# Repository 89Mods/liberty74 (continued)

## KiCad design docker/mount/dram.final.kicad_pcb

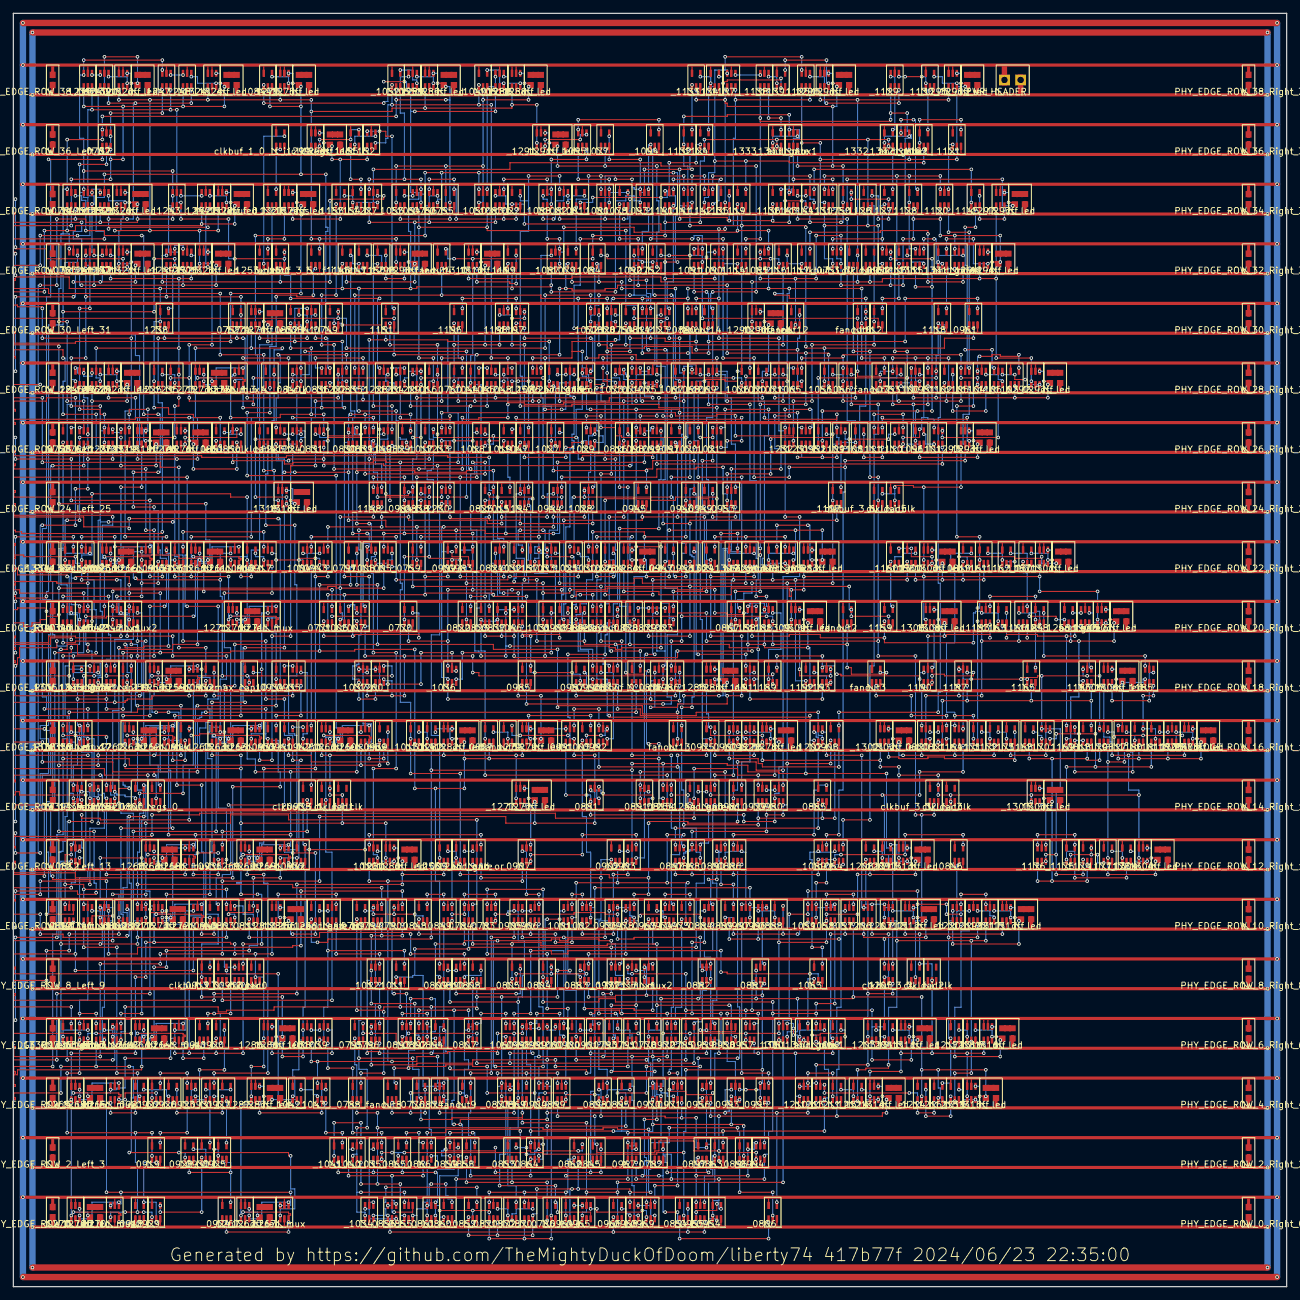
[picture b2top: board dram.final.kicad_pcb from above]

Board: 2 copper layers, 200.0 x 200.0 mm, 751 parts (0 on the bottom side), 638 nets.

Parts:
PHY_EDGE_ROW_0_Left_1, PHY_EDGE_ROW_0_Right_0, PHY_EDGE_ROW_2_Left_3, PHY_EDGE_ROW_2_Right_2, PHY_EDGE_ROW_4_Left_5, PHY_EDGE_ROW_4_Right_4, PHY_EDGE_ROW_6_Left_7, PHY_EDGE_ROW_6_Right_6, PHY_EDGE_ROW_8_Left_9, PHY_EDGE_ROW_8_Right_8, PHY_EDGE_ROW_10_Left_11, PHY_EDGE_ROW_10_Right_10, PHY_EDGE_ROW_12_Left_13, PHY_EDGE_ROW_12_Right_12, PHY_EDGE_ROW_14_Left_15, PHY_EDGE_ROW_14_Right_14, PHY_EDGE_ROW_16_Left_17, PHY_EDGE_ROW_16_Right_16, PHY_EDGE_ROW_18_Left_19, PHY_EDGE_ROW_18_Right_18, PHY_EDGE_ROW_20_Left_21, PHY_EDGE_ROW_20_Right_20, PHY_EDGE_ROW_22_Left_23, PHY_EDGE_ROW_22_Right_22, PHY_EDGE_ROW_24_Left_25, PHY_EDGE_ROW_24_Right_24, PHY_EDGE_ROW_26_Left_27, PHY_EDGE_ROW_26_Right_26, PHY_EDGE_ROW_28_Left_29, PHY_EDGE_ROW_28_Right_28, PHY_EDGE_ROW_30_Left_31, PHY_EDGE_ROW_30_Right_30, PHY_EDGE_ROW_32_Left_33, PHY_EDGE_ROW_32_Right_32, PHY_EDGE_ROW_34_Left_35, PHY_EDGE_ROW_34_Right_34, PHY_EDGE_ROW_36_Left_37, PHY_EDGE_ROW_36_Right_36, PHY_EDGE_ROW_38_Left_39, PHY_EDGE_ROW_38_Right_38: PWR_CAP; PWR_CAP_N
PWR_HEADER: PWR_HEADER; PWR_HEADER_N
_0749_, _0757_, _0759_, _0776_, _0782_, _0788_, _0791_, _0797_, _0822_, _0845_, _0846_, _0853_, _0911_, _0918_, _0921_, _0924_, _0945_, _0961_, _0985_, _1016_, _1077_, _1103_, _1126_, _1135_, _1168_, _1253__15: INV_74LVC1G04; INV_74LVC1G04_N
_0750_, _0752_, _0755_, _0800_, _0818_, _0819_, _0832_, _0850_, _0872_, _0878_, _0888_, _0896_, _0900_, _0912_, _0916_, _0919_, _0920_, _0922_, _0946_, _0947_, _0948_, _0952_, _0975_, _0984_, _1003_, _1009_, _1013_, _1017_, _1019_, _1020_, _1022_, _1044_, _1049_, _1052_, _1067_, _1076_, _1081_, _1084_, _1116_, _1118_, _1122_, _1134_, _1157_, _1159_, _1163_, _1165_, _1171_, _1174_, _1180_: OR2_74LVC1G32; OR2_74LVC1G32_N
_0751_, _0753_, _0838_, _0870_, _0876_, _0917_, _0935_, _0970_, _1033_, _1061_, _1120_, _1131_, _1158_, _1169_, _1183_, _1186_, _1188_, _1227_: NOR3_74LVC1G27; NOR3_74LVC1G27_N
_0754_, _0758_, _0760_, _0771_, _0778_, _0789_, _0793_, _0802_, _0804_, _0806_, _0823_, _0827_, _0829_, _0848_, _0851_, _0858_, _0860_, _0863_, _0865_, _0867_, _0885_, _0889_, _0897_, _0926_, _0928_, _0929_, _0949_, _0954_, _0981_, _0987_, _0988_, _1011_, _1014_, _1015_, _1026_, _1027_, _1032_, _1041_, _1042_, _1047_, _1097_, _1107_, _1108_, _1112_, _1117_, _1119_, _1127_, _1130_, _1132_, _1136_, _1139_, _1150_, _1155_, _1160_, _1167_, _1189_, _1192_, _1199_, _1204_, _1212_, _1215_, _1216_, _1218_, _1235_, _1238_, _1254__and_gate, _1255__and_gate, _1256__and_gate, _1257__and_gate, _1258__and_gate, _1328__and_gate, _1329__and_gate, _1330__and_gate, _1331__and_gate, _1332__and_gate, _1333__and_gate, _1334__and_gate, _1335__and_gate, _1336__and_gate: AND2_74LVC1G08; AND2_74LVC1G08_N
_0756_, _0803_, _0815_, _0835_, _0839_, _0856_, _0859_, _0861_, _0864_, _0866_, _0874_, _0877_, _0880_, _0882_, _0883_, _0886_, _0887_, _0891_, _0899_, _0901_, _0903_, _0943_, _0944_, _0956_, _0958_, _0959_, _0967_, _0976_, _0977_, _0993_, _0994_, _0998_, _0999_, _1000_, _1001_, _1002_, _1007_, _1021_, _1034_, _1035_, _1037_, _1045_, _1046_, _1050_, _1054_, _1058_, _1064_, _1065_, _1068_, _1082_, _1086_, _1092_, _1099_, _1106_, _1123_, _1142_, _1143_, _1144_, _1149_, _1152_, _1195_, _1197_, _1206_, _1220_, _1226_, _1229_, _1230_, _1232_, _1234_: NAND3_74LVC1G10; NAND3_74LVC1G10_N
_0761_, _0762_, _0763_, _0764_, _0799_, _0807_, _0904_, _0955_, _0971_, _1043_, _1057_, _1073_, _1222_, _1259__mux, _1260__mux, _1261__mux, _1262__mux, _1263__mux, _1264__mux, _1265__mux, _1266__mux, _1267__mux, _1268__mux, _1269__mux, _1270__mux, _1271__mux, _1272__mux, _1273__mux, _1328__mux1, _1329__mux1, _1330__mux1, _1331__mux1, _1332__mux1, _1333__mux1, _1334__mux1, _1335__mux1, _1336__mux1, _1337__mux1, _1337__mux2, _1338__mux1, _1338__mux2, _1339__mux1, _1339__mux2, _1340__mux1, _1340__mux2, _1341__mux1, _1341__mux2, _1342__mux1, _1342__mux2, _1343__mux1, _1343__mux2: MUX2_74LVC1G157; MUX2_74LVC1G157_N
_0770_, _0786_, _0816_, _0825_, _0852_, _0862_, _0869_, _0909_, _0925_, _0927_, _0930_, _0938_, _0941_, _1031_, _1063_, _1096_, _1102_, _1128_, _1153_, _1154_, _1161_, _1175_, _1178_, _1181_, _1184_, _1196_, _1209_: NOR2_74LVC1G02; NOR2_74LVC1G02_N
_0773_, _0783_, _0784_, _0790_, _0794_, _0796_, _0812_, _0813_, _0814_, _0828_, _0830_, _0841_, _0847_, _0849_, _0868_, _0871_, _0884_, _0892_, _0905_, _0906_, _0923_, _0931_, _0942_, _0957_, _0982_, _0992_, _1004_, _1010_, _1012_, _1030_, _1038_, _1051_, _1055_, _1060_, _1071_, _1075_, _1087_, _1088_, _1089_, _1109_, _1125_, _1137_, _1200_, _1202_, _1207_, _1210_, _1213_, _1221_, _1223_, _1233_, _1236_, _1241_, _1245_, _1249_: AND3_74LVC1G11; AND3_74LVC1G11_N
_0785_, _0795_, _0844_, _0854_, _0910_, _0914_, _0915_, _0932_, _0933_, _0934_, _0936_, _0937_, _0939_, _0940_, _1053_, _1062_, _1070_, _1078_, _1113_, _1121_, _1133_, _1156_, _1162_, _1177_, _1203_, _1208_, _1211_, _1214_, _1217_: XOR2_74LVC1G86; XOR2_74LVC1G86_N
_0801_, _0809_, _0817_, _0820_, _0821_, _0824_, _0836_, _0840_, _0890_, _0898_, _0950_, _0951_, _0965_, _0986_, _0989_, _0996_, _1028_, _1066_, _1083_, _1091_, _1100_, _1105_, _1129_, _1138_, _1148_, _1164_, _1166_, _1179_, _1187_, _1191_, _1194_, _1231_: OR3_74LVC1G332; OR3_74LVC1G332_N
_0805_, _0808_, _0811_, _0837_, _0894_, _0895_, _0902_, _0908_, _0963_, _0964_, _0966_, _0973_, _0983_, _1006_, _1024_, _1056_, _1079_, _1094_, _1114_, _1124_, _1145_, _1146_, _1147_, _1151_, _1172_, _1173_, _1225_: NAND2_74LVC1G00; NAND2_74LVC1G00_N
_0810_, _0831_, _0855_, _0873_, _0879_, _0881_, _0893_, _0907_, _0913_, _0953_, _0960_, _0968_, _0969_, _0972_, _0974_, _0978_, _0979_, _0980_, _0990_, _0991_, _0995_, _0997_, _1005_, _1008_, _1018_, _1023_, _1025_, _1029_, _1036_, _1039_, _1040_, _1048_, _1059_, _1069_, _1072_, _1074_, _1080_, _1085_, _1090_, _1093_, _1095_, _1098_, _1101_, _1104_, _1110_, _1111_, _1115_, _1140_, _1141_, _1170_, _1176_, _1182_, _1185_, _1190_, _1193_, _1198_, _1205_, _1219_, _1224_, _1228_, _1237_, _1239_, _1240_, _1242_, _1243_, _1244_, _1246_, _1247_, _1248_, _1250_, _1251_, _1252_, _1254__and_or, _1255__and_or, _1256__and_or, _1257__and_or, _1258__and_or: AO21_74LVC1G0832; AO21_74LVC1G0832_N
_1259__dff, _1260__dff, _1261__dff, _1262__dff, _1263__dff, _1264__dff, _1265__dff, _1266__dff, _1267__dff, _1268__dff, _1269__dff, _1270__dff, _1271__dff, _1272__dff, _1273__dff, _1274__dff, _1275__dff, _1276__dff, _1277__dff, _1278__dff, _1279__dff, _1280__dff, _1281__dff, _1282__dff, _1283__dff, _1284__dff, _1285__dff, _1286__dff, _1287__dff, _1288__dff, _1289__dff, _1290__dff, _1291__dff, _1292__dff, _1293__dff, _1294__dff, _1295__dff, _1296__dff, _1297__dff, _1298__dff, _1299__dff, _1300__dff, _1301__dff, _1302__dff, _1303__dff, _1304__dff, _1305__dff, _1306__dff, _1307__dff, _1308__dff, _1309__dff, _1310__dff, _1311__dff, _1312__dff, _1313__dff, _1314__dff, _1315__dff, _1316__dff, _1317__dff, _1318__dff, _1319__dff, _1320__dff, _1321__dff, _1322__dff, _1323__dff, _1324__dff, _1325__dff, _1326__dff, _1327__dff: DFF_74LVC1G175; DFF_74LVC1G175_N
_1259__led, _1260__led, _1261__led, _1262__led, _1263__led, _1264__led, _1265__led, _1266__led, _1267__led, _1268__led, _1269__led, _1270__led, _1271__led, _1272__led, _1273__led, _1274__led, _1275__led, _1276__led, _1277__led, _1278__led, _1279__led, _1280__led, _1281__led, _1282__led, _1283__led, _1284__led, _1285__led, _1286__led, _1287__led, _1288__led, _1289__led, _1290__led, _1291__led, _1292__led, _1293__led, _1294__led, _1295__led, _1296__led, _1297__led, _1298__led, _1299__led, _1300__led, _1301__led, _1302__led, _1303__led, _1304__led, _1305__led, _1306__led, _1307__led, _1308__led, _1309__led, _1310__led, _1311__led, _1312__led, _1313__led, _1314__led, _1315__led, _1316__led, _1317__led, _1318__led, _1319__led, _1320__led, _1321__led, _1322__led, _1323__led, _1324__led, _1325__led, _1326__led, _1327__led: Led_Res_0603; Led_Res_0603_N
clkbuf_0_i_clk, clkbuf_0_i_clk_regs, clkbuf_1_0__f_i_clk_regs, clkbuf_3_0__f_i_clk, clkbuf_3_1__f_i_clk, clkbuf_3_2__f_i_clk, clkbuf_3_3__f_i_clk, clkbuf_3_4__f_i_clk, clkbuf_3_5__f_i_clk, clkbuf_3_6__f_i_clk, clkbuf_3_7__f_i_clk: BUF_74LVC1G125; BUF_74LVC1G125_N
clkbuf_regs_0_: BUF_74LVC1G125; BUF_74LVC1G125_N
clkload0, clkload1, clkload2, clkload3, clkload4, clkload5, clkload6: BUF_74LVC1G125; BUF_74LVC1G125_N
delaybuf_0_: BUF_74LVC1G125; BUF_74LVC1G125_N
fanout1, fanout2, fanout3, fanout4, fanout5, fanout6, fanout7, fanout8, fanout9, fanout12, fanout13, fanout14: BUF_74LVC1G125; BUF_74LVC1G125_N
max_cap10, max_cap11: BUF_74LVC1G125; BUF_74LVC1G125_N

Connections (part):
A_f[10]: _0773_.3 (B), _0932_.1 (B), _1259__mux.1 (I1)
A_f[11]: _0939_.1 (B), _1260__mux.1 (I1), _1338__mux1.1 (I1)
A_f[12]: _0910_.1 (B), _1261__mux.1 (I1), _1334__mux1.1 (I1)
A_f[13]: _0914_.1 (B), _1262__mux.1 (I1), _1335__mux1.1 (I1)
A_f[14]: _0933_.1 (B), _1263__mux.1 (I1), _1339__mux1.1 (I1)
A_f[15]: _0913_.3 (B), _0920_.1 (B), _1264__mux.1 (I1), _1340__mux1.1 (I1)
A_f[16]: _0921_.2 (A), _1265__mux.1 (I1), _1341__mux1.1 (I1)
A_f[17]: _0915_.1 (B), _1266__mux.1 (I1), _1342__mux1.1 (I1)
A_f[18]: _0925_.1 (B), _0928_.1 (B), _1267__mux.1 (I1), _1343__mux1.1 (I1)
A_f[19]: _0799_.1 (I1), _0936_.1 (B), _1268__mux.1 (I1)
A_f[20]: _0803_.3 (B), _0937_.1 (B), _1269__mux.1 (I1)
A_f[21]: _0919_.1 (B), _0929_.1 (B), _1270__mux.1 (I1), _1336__mux1.1 (I1)
A_f[22]: _0812_.3 (B), _0934_.1 (B), _1271__mux.1 (I1)
A_f[23]: _0813_.3 (B), _0940_.1 (B), _1272__mux.1 (I1)
BA[0]: _0912_.1 (B), _1038_.1 (A), _1286__dff.4 (Q), _1286__led.1 (I)
BA[1]: _0912_.2 (A), _1042_.2 (A), _1287__dff.4 (Q), _1287__led.1 (I)
CAS_b: _0991_.6 (C), _1279__dff.4 (Q), _1279__led.1 (I)
CE_edge: _0836_.1 (A), _1222_.6 (S), _1273__dff.4 (Q), _1273__led.1 (I), _1273__mux.3 (I0)
CE_edge_edge: _0832_.2 (A), _1222_.3 (I0), _1274__dff.4 (Q), _1274__led.1 (I)
CEb_in: _0757_.2 (A), _0840_.1 (A), _1225_.2 (A), _1238_.2 (A), _1273__mux.1 (I1)
CKE: _1256__and_gate.2 (A), _1281__dff.4 (Q), _1281__led.1 (I)
CS_b: _0881_.6 (C), _1277__dff.4 (Q), _1277__led.1 (I)
DQS: _1327__dff.4 (Q), _1327__led.1 (I)
DQS_l: _1152_.1 (A), _1153_.2 (A), _1299__dff.4 (Q), _1299__led.1 (I), _1327__dff.3 (D)
GND: PHY_EDGE_ROW_0_Left_1.1 (GND), PHY_EDGE_ROW_0_Right_0.1 (GND), PHY_EDGE_ROW_2_Left_3.1 (GND), PHY_EDGE_ROW_2_Right_2.1 (GND), PHY_EDGE_ROW_4_Left_5.1 (GND), PHY_EDGE_ROW_4_Right_4.1 (GND), PHY_EDGE_ROW_6_Left_7.1 (GND), PHY_EDGE_ROW_6_Right_6.1 (GND), PHY_EDGE_ROW_8_Left_9.1 (GND), PHY_EDGE_ROW_8_Right_8.1 (GND), PHY_EDGE_ROW_10_Left_11.1 (GND), PHY_EDGE_ROW_10_Right_10.1 (GND), PHY_EDGE_ROW_12_Left_13.1 (GND), PHY_EDGE_ROW_12_Right_12.1 (GND), PHY_EDGE_ROW_14_Left_15.1 (GND), PHY_EDGE_ROW_14_Right_14.1 (GND), PHY_EDGE_ROW_16_Left_17.1 (GND), PHY_EDGE_ROW_16_Right_16.1 (GND), PHY_EDGE_ROW_18_Left_19.1 (GND), PHY_EDGE_ROW_18_Right_18.1 (GND), PHY_EDGE_ROW_20_Left_21.1 (GND), PHY_EDGE_ROW_20_Right_20.1 (GND), PHY_EDGE_ROW_22_Left_23.1 (GND), PHY_EDGE_ROW_22_Right_22.1 (GND), PHY_EDGE_ROW_24_Left_25.1 (GND), PHY_EDGE_ROW_24_Right_24.1 (GND), PHY_EDGE_ROW_26_Left_27.1 (GND), PHY_EDGE_ROW_26_Right_26.1 (GND), PHY_EDGE_ROW_28_Left_29.1 (GND), PHY_EDGE_ROW_28_Right_28.1 (GND), PHY_EDGE_ROW_30_Left_31.1 (GND), PHY_EDGE_ROW_30_Right_30.1 (GND), PHY_EDGE_ROW_32_Left_33.1 (GND), PHY_EDGE_ROW_32_Right_32.1 (GND), PHY_EDGE_ROW_34_Left_35.1 (GND), PHY_EDGE_ROW_34_Right_34.1 (GND), PHY_EDGE_ROW_36_Left_37.1 (GND), PHY_EDGE_ROW_36_Right_36.1 (GND), PHY_EDGE_ROW_38_Left_39.1 (GND), PHY_EDGE_ROW_38_Right_38.1 (GND), PWR_HEADER.2 (GND), _0749_.1 (GND), _0749_.3 (GND), _0750_.3 (GND), _0751_.2 (GND), _0752_.3 (GND), _0753_.2 (GND), _0754_.3 (GND), _0755_.3 (GND), _0756_.2 (GND), _0757_.1 (GND), _0757_.3 (GND), _0758_.3 (GND), _0759_.1 (GND), _0759_.3 (GND), _0760_.3 (GND), _0761_.2 (GND), _0762_.2 (GND), _0763_.2 (GND), _0764_.2 (GND), _0770_.3 (GND), _0771_.3 (GND), _0773_.2 (GND), _0776_.1 (GND), _0776_.3 (GND), _0778_.3 (GND), _0782_.1 (GND), _0782_.3 (GND), _0783_.2 (GND), _0784_.2 (GND), _0785_.3 (GND), _0786_.3 (GND), _0788_.1 (GND), _0788_.3 (GND), _0789_.3 (GND), _0790_.2 (GND), _0791_.1 (GND), _0791_.3 (GND), _0793_.3 (GND), _0794_.2 (GND)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
ODT: _0850_.2 (A), _1276__dff.4 (Q), _1276__led.1 (I)
Q[0]: _0761_.4 (Y), _1245_.3 (B)
Q[1]: _0762_.4 (Y), _1247_.1 (A)
Q[2]: _0763_.4 (Y), _1249_.3 (B)
Q[3]: _0764_.4 (Y), _1251_.1 (A)
Q_f[0]: _0761_.1 (I1), _1237_.1 (A), _1319__dff.4 (Q), _1319__led.1 (I)
Q_f[1]: _0762_.1 (I1), _1240_.1 (A), _1320__dff.4 (Q), _1320__led.1 (I)
Q_f[2]: _0763_.1 (I1), _1242_.1 (A), _1321__dff.4 (Q), _1321__led.1 (I)
Q_f[3]: _0764_.1 (I1), _1244_.1 (A), _1322__dff.4 (Q), _1322__led.1 (I)
Q_f[4]: _0761_.3 (I0), _1236_.3 (B), _1246_.1 (A), _1323__dff.4 (Q), _1323__led.1 (I)
Q_f[5]: _0762_.3 (I0), _1239_.1 (A), _1248_.1 (A), _1324__dff.4 (Q), _1324__led.1 (I)
Q_f[6]: _0763_.3 (I0), _1241_.3 (B), _1250_.1 (A), _1325__dff.4 (Q), _1325__led.1 (I)
Q_f[7]: _0764_.3 (I0), _1243_.1 (A), _1252_.1 (A), _1326__dff.4 (Q), _1326__led.1 (I)
RAS_b: _0979_.6 (C), _1254__and_gate.2 (A), _1278__dff.4 (Q), _1278__led.1 (I)
VDD: PHY_EDGE_ROW_0_Left_1.2 (VDD), PHY_EDGE_ROW_0_Right_0.2 (VDD), PHY_EDGE_ROW_2_Left_3.2 (VDD), PHY_EDGE_ROW_2_Right_2.2 (VDD), PHY_EDGE_ROW_4_Left_5.2 (VDD), PHY_EDGE_ROW_4_Right_4.2 (VDD), PHY_EDGE_ROW_6_Left_7.2 (VDD), PHY_EDGE_ROW_6_Right_6.2 (VDD), PHY_EDGE_ROW_8_Left_9.2 (VDD), PHY_EDGE_ROW_8_Right_8.2 (VDD), PHY_EDGE_ROW_10_Left_11.2 (VDD), PHY_EDGE_ROW_10_Right_10.2 (VDD), PHY_EDGE_ROW_12_Left_13.2 (VDD), PHY_EDGE_ROW_12_Right_12.2 (VDD), PHY_EDGE_ROW_14_Left_15.2 (VDD), PHY_EDGE_ROW_14_Right_14.2 (VDD), PHY_EDGE_ROW_16_Left_17.2 (VDD), PHY_EDGE_ROW_16_Right_16.2 (VDD), PHY_EDGE_ROW_18_Left_19.2 (VDD), PHY_EDGE_ROW_18_Right_18.2 (VDD), PHY_EDGE_ROW_20_Left_21.2 (VDD), PHY_EDGE_ROW_20_Right_20.2 (VDD), PHY_EDGE_ROW_22_Left_23.2 (VDD), PHY_EDGE_ROW_22_Right_22.2 (VDD), PHY_EDGE_ROW_24_Left_25.2 (VDD), PHY_EDGE_ROW_24_Right_24.2 (VDD), PHY_EDGE_ROW_26_Left_27.2 (VDD), PHY_EDGE_ROW_26_Right_26.2 (VDD), PHY_EDGE_ROW_28_Left_29.2 (VDD), PHY_EDGE_ROW_28_Right_28.2 (VDD), PHY_EDGE_ROW_30_Left_31.2 (VDD), PHY_EDGE_ROW_30_Right_30.2 (VDD), PHY_EDGE_ROW_32_Left_33.2 (VDD), PHY_EDGE_ROW_32_Right_32.2 (VDD), PHY_EDGE_ROW_34_Left_35.2 (VDD), PHY_EDGE_ROW_34_Right_34.2 (VDD), PHY_EDGE_ROW_36_Left_37.2 (VDD), PHY_EDGE_ROW_36_Right_36.2 (VDD), PHY_EDGE_ROW_38_Left_39.2 (VDD), PHY_EDGE_ROW_38_Right_38.2 (VDD), PWR_HEADER.1 (VDD), _0749_.6 (VDD), _0750_.6 (VDD), _0751_.5 (VDD), _0752_.6 (VDD), _0753_.5 (VDD), _0754_.6 (VDD), _0755_.6 (VDD), _0756_.5 (VDD), _0757_.6 (VDD), _0758_.6 (VDD), _0759_.6 (VDD), _0760_.6 (VDD), _0761_.5 (VDD), _0762_.5 (VDD), _0763_.5 (VDD), _0764_.5 (VDD), _0770_.6 (VDD), _0771_.6 (VDD), _0773_.5 (VDD), _0776_.6 (VDD), _0778_.6 (VDD), _0782_.6 (VDD), _0783_.5 (VDD), _0784_.5 (VDD), _0785_.6 (VDD), _0786_.6 (VDD), _0788_.6 (VDD), _0789_.6 (VDD), _0790_.5 (VDD), _0791_.6 (VDD), _0793_.6 (VDD), _0794_.5 (VDD), _0795_.6 (VDD), _0796_.5 (VDD), _0797_.6 (VDD), _0799_.5 (VDD), _0800_.6 (VDD), _0801_.5 (VDD), _0802_.6 (VDD)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
WE_b: _1009_.2 (A), _1280__dff.4 (Q), _1280__led.1 (I)
WEb_f: _0758_.1 (B), _1005_.1 (A), _1006_.1 (B), _1017_.2 (A), _1148_.1 (A), _1151_.1 (B), _1257__and_gate.1 (B)
_0001_: _0841_.4 (Y), _1274__dff.3 (D)
_0002_: _0844_.4 (Y), _1275__dff.3 (D)
_0003_: _0851_.4 (Y), _1276__dff.3 (D)
_0004_: _0907_.4 (Y), _1277__dff.3 (D)
_0005_: _0982_.4 (Y), _1278__dff.3 (D)
_0006_: _1003_.4 (Y), _1279__dff.3 (D)
_0007_: _1010_.4 (Y), _1280__dff.3 (D)
_0008_: _1256__and_or.4 (Y), _1281__dff.3 (D)
_0009_: _1014_.4 (Y), _1282__dff.3 (D)
_0010_: _1283__dff.3 (D), _1328__and_gate.4 (Y)
_0011_: _1030_.4 (Y), _1284__dff.3 (D)
_0012_: _1285__dff.3 (D), _1329__and_gate.4 (Y)
_0013_: _1039_.4 (Y), _1286__dff.3 (D)
_0014_: _1043_.4 (Y), _1287__dff.3 (D)
_0015_: _1051_.4 (Y), _1288__dff.3 (D)
_0016_: _1055_.4 (Y), _1289__dff.3 (D)
_0017_: _1076_.4 (Y), _1290__dff.3 (D)
_0018_: _1095_.4 (Y), _1291__dff.3 (D)
_0019_: _1106_.4 (Y), _1292__dff.3 (D)
_0020_: _1111_.4 (Y), _1293__dff.3 (D)
_0021_: _1294__dff.3 (D), _1331__and_gate.4 (Y)
_0022_: _1130_.4 (Y), _1295__dff.3 (D)
_0023_: _1139_.4 (Y), _1296__dff.3 (D)
_0024_: _1145_.4 (Y), _1297__dff.3 (D)
_0025_: _1150_.4 (Y), _1298__dff.3 (D)
_0026_: _1155_.4 (Y), _1299__dff.3 (D)
_0027_: _1160_.4 (Y), _1300__dff.3 (D)
_0028_: _1167_.4 (Y), _1301__dff.3 (D)
_0029_: _1173_.4 (Y), _1302__dff.3 (D)
_0030_: _1176_.4 (Y), _1303__dff.3 (D)
_0031_: _1178_.4 (Y), _1304__dff.3 (D)
_0032_: _1182_.4 (Y), _1305__dff.3 (D)
_0033_: _1185_.4 (Y), _1306__dff.3 (D)
_0034_: _1258__and_or.4 (Y), _1307__dff.3 (D)
_0035_: _1190_.4 (Y), _1308__dff.3 (D)
_0036_: _1193_.4 (Y), _1309__dff.3 (D)
_0037_: _1199_.4 (Y), _1310__dff.3 (D)
_0052_: _1204_.4 (Y), _1311__dff.3 (D)
_0053_: _1207_.4 (Y), _1312__dff.3 (D)
_0054_: _1209_.4 (Y), _1313__dff.3 (D)
_0055_: _1212_.4 (Y), _1314__dff.3 (D)
_0056_: _1215_.4 (Y), _1315__dff.3 (D)
_0057_: _1218_.4 (Y), _1316__dff.3 (D)
_0058_: _1221_.4 (Y), _1317__dff.3 (D)
_0059_: _1224_.4 (Y), _1318__dff.3 (D)
_0061_: _1237_.4 (Y), _1319__dff.3 (D)
_0062_: _1240_.4 (Y), _1320__dff.3 (D)
_0063_: _1242_.4 (Y), _1321__dff.3 (D)
_0064_: _1244_.4 (Y), _1322__dff.3 (D)
_0065_: _1246_.4 (Y), _1323__dff.3 (D)
_0066_: _1248_.4 (Y), _1324__dff.3 (D)
_0067_: _1250_.4 (Y), _1325__dff.3 (D)
_0068_: _1252_.4 (Y), _1326__dff.3 (D)
_0070_: _0750_.4 (Y), _0751_.6 (C), _0950_.6 (C), _1127_.1 (B)
_0071_: _0751_.4 (Y), _1085_.1 (A), fanout12.2 (A)
_0072_: _0752_.4 (Y), _0753_.6 (C), _0951_.6 (C), _1091_.3 (B), _1100_.3 (B), _1102_.2 (A)
_0073_: _0753_.4 (Y), fanout7.2 (A)
_0074_: _0754_.4 (Y), _0756_.3 (B), _1050_.6 (C), _1054_.3 (B), _1090_.1 (A), _1123_.1 (A)
_0075_: _0755_.4 (Y), _0756_.6 (C), _1022_.2 (A), _1083_.3 (B)
_0076_: _0757_.4 (Y), _0758_.2 (A), _1222_.1 (I1), _1236_.1 (A), _1241_.1 (A), _1245_.1 (A), _1249_.1 (A)
_0077_: _0759_.4 (Y), _0760_.2 (A), _0840_.3 (B), _1044_.2 (A), _1086_.1 (A), _1157_.2 (A)
_0083_: _0770_.4 (Y), _0771_.1 (B), _1007_.1 (A)
_0084_: _0771_.4 (Y), _0773_.6 (C), _1334__mux1.6 (S), _1340__mux1.6 (S), _1342__mux1.6 (S), max_cap11.2 (A)
_0088_: _0776_.4 (Y), _0807_.6 (S), fanout8.2 (A), fanout9.2 (A)
_0090_: _0778_.4 (Y), _0784_.3 (B), _0805_.1 (B), _0958_.3 (B), _0963_.2 (A)
_0094_: _0782_.4 (Y), _0783_.6 (C), _0804_.1 (B), _0954_.1 (B), _0967_.3 (B), _0994_.3 (B), _1058_.3 (B), _1330__mux1.6 (S)
_0095_: _0783_.4 (Y), _0784_.6 (C), _0849_.3 (B)
_0096_: _0784_.4 (Y), _0801_.3 (B), _1338__mux2.3 (I0), _1339__mux2.3 (I0), _1340__mux2.3 (I0)
_0102_: _0785_.4 (Y), _0790_.1 (A), _0807_.3 (I0), _0882_.6 (C), _0893_.1 (A), _0998_.3 (B)
_0103_: _0786_.4 (Y), _0790_.3 (B), _0794_.3 (B), _0796_.3 (B), _0894_.2 (A), _0965_.3 (B), _0998_.6 (C), _1012_.6 (C), _1060_.3 (B)
_0105_: _0788_.4 (Y), _0789_.1 (B), _0808_.2 (A), _0873_.6 (C), _0883_.1 (A), _0892_.3 (B), _1001_.1 (A), _1011_.2 (A), _1060_.1 (A)
_0106_: _0789_.4 (Y), _0790_.6 (C), _0794_.6 (C), _0848_.2 (A)
_0107_: _0790_.4 (Y), _1341__mux2.3 (I0)
_0109_: _0791_.4 (Y), _0793_.2 (A), _1337__mux1.3 (I0)
_0111_: _0793_.4 (Y), _0794_.1 (A), _0796_.1 (A), _0976_.6 (C), _0999_.3 (B), _1012_.3 (B)
_0112_: _0794_.4 (Y), _0801_.6 (C), _1342__mux2.3 (I0)
_0114_: _0795_.4 (Y), _0796_.6 (C), _0893_.3 (B)
_0115_: _0796_.4 (Y), _1343__mux2.3 (I0)
_0117_: _0797_.4 (Y), _0800_.2 (A), _1065_.1 (A), fanout13.2 (A)
_0119_: _0799_.4 (Y), _0800_.1 (B)
_0120_: _0800_.4 (Y), _0802_.2 (A)
_0121_: _0801_.4 (Y), _0802_.1 (B)
_0122_: _0803_.4 (Y), _0811_.2 (A)
_0123_: _0804_.4 (Y), _0805_.2 (A), _0883_.6 (C), _1337__mux2.3 (I0)
_0124_: _0805_.4 (Y), _0810_.1 (A)
_0125_: _0806_.4 (Y), _0807_.1 (I1), _0859_.3 (B), _0861_.3 (B), _0892_.6 (C), _0904_.3 (I0), _0993_.6 (C), _1210_.3 (B), _1213_.1 (A)
_0126_: _0807_.4 (Y), _0808_.1 (B), _1060_.6 (C)
_0127_: _0808_.4 (Y), _0810_.3 (B)
_0128_: _0809_.4 (Y), _0810_.6 (C)
_0129_: _0810_.4 (Y), _0811_.1 (B)
_0131_: _0814_.4 (Y), _0816_.2 (A), _0836_.3 (B), _1017_.1 (B), _1048_.6 (C), _1081_.2 (A), _1140_.6 (C), _1153_.1 (B)
_0132_: _0815_.4 (Y), _0816_.1 (B), _1254__and_gate.1 (B)
_0133_: _0816_.4 (Y), _0831_.3 (B), _1009_.1 (B), _1073_.3 (I0), _1223_.3 (B), _1228_.1 (A)
_0134_: _0817_.4 (Y), _0818_.1 (B), _1169_.3 (B)
_0135_: _0818_.4 (Y), _0821_.1 (A), _1165_.2 (A), _1186_.3 (B), _1187_.3 (B)
_0136_: _0819_.4 (Y), _0821_.3 (B), _1164_.6 (C), _1171_.1 (B)
_0137_: _0820_.4 (Y), _0821_.6 (C)
_0138_: _0821_.4 (Y), fanout3.2 (A)
_0139_: _0822_.4 (Y), _0823_.1 (B), _0837_.1 (B), _1046_.6 (C)
_0140_: _0823_.4 (Y), _0825_.2 (A), _1028_.3 (B), _1194_.1 (A), _1230_.3 (B)
_0141_: _0824_.4 (Y), _0825_.1 (B), _1033_.1 (A), _1157_.1 (B), _1194_.3 (B)
_0142_: _0825_.4 (Y), _0830_.3 (B), _1008_.1 (A), _1045_.1 (A), _1229_.1 (A)
_0144_: _0827_.4 (Y), fanout5.2 (A)
_0145_: _0828_.4 (Y), _0829_.1 (B), _1027_.1 (B), _1086_.6 (C), _1149_.3 (B), _1195_.3 (B), _1229_.3 (B)
_0146_: _0829_.4 (Y), _0830_.6 (C), _0839_.6 (C), _1007_.3 (B), _1037_.3 (B), _1189_.2 (A), _1200_.3 (B)
_0147_: _0830_.4 (Y), _0831_.6 (C)
_0148_: _0831_.4 (Y), _0832_.1 (B), _1273__mux.6 (S)
_0149_: _0832_.4 (Y), _0841_.1 (A)
_0152_: _0835_.4 (Y), _0836_.6 (C)
_0153_: _0836_.4 (Y), _0841_.3 (B)
_0154_: _0837_.4 (Y), _0839_.1 (A), _1023_.1 (A)
_0155_: _0838_.4 (Y), _0839_.3 (B), _1149_.1 (A), _1230_.6 (C)
_0156_: _0839_.4 (Y), _0840_.6 (C), _1224_.3 (B)
_0157_: _0840_.4 (Y), _0841_.6 (C)
_0160_: _0845_.4 (Y), _0849_.1 (A), _0859_.1 (A), _0884_.1 (A), _0958_.1 (A), _0972_.6 (C), _0977_.3 (B), _0993_.3 (B)
_0161_: _0846_.4 (Y), _0847_.1 (A), _0868_.1 (A), _0886_.1 (A), _1064_.1 (A), _1089_.1 (A)
_0162_: _0847_.4 (Y), _0848_.1 (B), _0902_.2 (A), _0906_.1 (A), _0973_.2 (A), _1001_.3 (B)
_0163_: _0848_.4 (Y), _0849_.6 (C)
_0164_: _0849_.4 (Y), _0850_.1 (B), _1013_.1 (B), _1196_.1 (B)
_0165_: _0850_.4 (Y), _0851_.1 (B)
_0166_: _0852_.4 (Y), _0856_.1 (A), _1034_.3 (B)
_0167_: _0853_.4 (Y), _0854_.2 (A), _0855_.3 (B), _0861_.1 (A), _0883_.3 (B), _0887_.3 (B), _0995_.6 (C), _1337__mux2.6 (S)
_0168_: _0854_.4 (Y), _0856_.3 (B), _0955_.3 (I0), _0966_.1 (B), _1034_.6 (C)
_0169_: _0855_.4 (Y), _0856_.6 (C)
_0170_: _0856_.4 (Y), _0866_.1 (A), _1040_.6 (C)
_0172_: _0858_.4 (Y), _0859_.6 (C)
_0173_: _0859_.4 (Y), _0866_.3 (B)
_0174_: _0860_.4 (Y), _0861_.6 (C)
_0175_: _0861_.4 (Y), _0865_.2 (A), _1035_.1 (A), _1041_.2 (A)
_0176_: _0862_.4 (Y), _0864_.3 (B), _0898_.1 (A), _0899_.3 (B), _0904_.1 (I1)
_0177_: _0863_.4 (Y), _0864_.6 (C), _0895_.1 (B), _0967_.6 (C), _0999_.6 (C), _1213_.3 (B), _1330__mux1.3 (I0)
_0178_: _0864_.4 (Y), _0865_.1 (B), _1035_.3 (B)
_0179_: _0865_.4 (Y), _0866_.6 (C)
_0180_: _0866_.4 (Y), _0874_.1 (A)
_0181_: _0867_.4 (Y), _0868_.6 (C), _0908_.1 (B), _0979_.3 (B), _0980_.3 (B), _1070_.1 (B), _1107_.1 (B), _1109_.6 (C)
_0182_: _0868_.4 (Y), _0874_.3 (B), _0977_.6 (C), _1011_.1 (B), _1254__and_or.1 (A), _1255__and_or.1 (A)
_0183_: _0869_.4 (Y), _0873_.1 (A), _0899_.6 (C)
_0184_: _0870_.4 (Y), _0872_.2 (A)
_0185_: _0871_.4 (Y), _0872_.1 (B)
_0186_: _0872_.4 (Y), _0873_.3 (B)
_0187_: _0873_.4 (Y), _0874_.6 (C)
_0188_: _0874_.4 (Y), _0907_.1 (A), _1010_.1 (A), _1038_.3 (B), _1043_.6 (S)
_0190_: _0876_.4 (Y), _0879_.3 (B), _1023_.3 (B), _1098_.1 (A), _1123_.6 (C)
_0191_: _0877_.4 (Y), _0878_.1 (B), _0989_.3 (B), _1069_.1 (A), _1158_.3 (B), _1191_.3 (B), _1194_.6 (C)
_0192_: _0878_.4 (Y), _0879_.6 (C), _1023_.6 (C)
_0193_: _0879_.4 (Y), _0891_.1 (A)
_0194_: _0880_.4 (Y), _0881_.1 (A), _0980_.1 (A), _0991_.1 (A), _1022_.1 (B), _1083_.6 (C), _1125_.3 (B), _1137_.3 (B), _1232_.1 (A)
_0195_: _0881_.4 (Y), _0891_.3 (B)
_0196_: _0882_.4 (Y), _0884_.3 (B)
_0197_: _0883_.4 (Y), _0884_.6 (C), _0978_.1 (A)
_0198_: _0884_.4 (Y), _0890_.1 (A)
_0199_: _0885_.4 (Y), _0886_.6 (C), _1202_.6 (C)
_0200_: _0886_.4 (Y), _0890_.3 (B), _0997_.6 (C)
_0201_: _0887_.4 (Y), _0888_.1 (B), _0996_.6 (C)
_0202_: _0888_.4 (Y), _0889_.1 (B), _1059_.1 (A)
_0203_: _0889_.4 (Y), _0890_.6 (C)
_0204_: _0890_.4 (Y), _0891_.6 (C)
_0205_: _0891_.4 (Y), _0903_.3 (B)
_0206_: _0892_.4 (Y), _0893_.6 (C)
_0207_: _0893_.4 (Y), _0894_.1 (B)
_0208_: _0894_.4 (Y), _0901_.1 (A), _0959_.1 (A)
_0209_: _0895_.4 (Y), _0898_.3 (B)
_0210_: _0896_.4 (Y), _0897_.1 (B), _0955_.6 (S), _0994_.6 (C)
_0211_: _0897_.4 (Y), _0898_.6 (C), _0971_.3 (I0)
_0212_: _0898_.4 (Y), _0901_.3 (B)
_0213_: _0899_.4 (Y), _0900_.1 (B), _1000_.1 (A)
_0214_: _0900_.4 (Y), _0901_.6 (C)
_0215_: _0901_.4 (Y), _0902_.1 (B), _1255__and_or.3 (B)
_0216_: _0902_.4 (Y), _0903_.6 (C)
_0217_: _0903_.4 (Y), _0907_.3 (B)
_0218_: _0904_.4 (Y), _0906_.3 (B)
_0219_: _0905_.4 (Y), _0906_.6 (C)
_0220_: _0906_.4 (Y), _0907_.6 (C)
_0221_: _0908_.4 (Y), _0960_.1 (A), _1118_.1 (B)
_0222_: _0909_.4 (Y), _0944_.3 (B), _1015_.2 (A), _1037_.1 (A), _1086_.3 (B), _1200_.1 (A), _1257__and_or.1 (A)
_0223_: _0910_.4 (Y), _0917_.1 (A)
_0224_: _0911_.4 (Y), _0913_.1 (A), _0920_.2 (A)
_0225_: _0912_.4 (Y), _0913_.6 (C)
_0226_: _0913_.4 (Y), _0917_.3 (B)
_0227_: _0914_.4 (Y), _0916_.2 (A)
_0228_: _0915_.4 (Y), _0916_.1 (B)
_0229_: _0916_.4 (Y), _0917_.6 (C)
_0230_: _0917_.4 (Y), _0943_.1 (A), _1004_.1 (A)
_0231_: _0918_.4 (Y), _0919_.2 (A), _0929_.2 (A)
_0232_: _0919_.4 (Y), _0923_.1 (A)
_0233_: _0920_.4 (Y), _0923_.3 (B)
_0234_: _0921_.4 (Y), _0922_.1 (B), _0926_.1 (B)
_0235_: _0922_.4 (Y), _0923_.6 (C)
_0236_: _0923_.4 (Y), _0931_.1 (A)
_0237_: _0924_.4 (Y), _0925_.2 (A), _0928_.2 (A)
_0238_: _0925_.4 (Y), _0927_.2 (A)
_0239_: _0926_.4 (Y), _0927_.1 (B)
_0240_: _0927_.4 (Y), _0931_.3 (B)
_0241_: _0928_.4 (Y), _0930_.2 (A)
_0242_: _0929_.4 (Y), _0930_.1 (B)
_0243_: _0930_.4 (Y), _0931_.6 (C)
_0244_: _0931_.4 (Y), _0943_.3 (B), _1004_.3 (B)
_0245_: _0932_.4 (Y), _0935_.1 (A)
_0246_: _0933_.4 (Y), _0935_.3 (B)
_0247_: _0934_.4 (Y), _0935_.6 (C)
_0248_: _0935_.4 (Y), _0942_.1 (A)
_0249_: _0936_.4 (Y), _0938_.2 (A)
_0250_: _0937_.4 (Y), _0938_.1 (B)
_0251_: _0938_.4 (Y), _0942_.3 (B)
_0252_: _0939_.4 (Y), _0941_.2 (A)
_0253_: _0940_.4 (Y), _0941_.1 (B)
_0254_: _0941_.4 (Y), _0942_.6 (C)
_0255_: _0942_.4 (Y), _0943_.6 (C), _1004_.6 (C)
_0256_: _0943_.4 (Y), _0944_.6 (C), _0984_.2 (A), _1015_.1 (B), _1148_.3 (B)
_0257_: _0944_.4 (Y), _0953_.1 (A)
_0258_: _0945_.4 (Y), _0946_.2 (A), _1020_.2 (A), _1027_.2 (A), _1257__and_gate.2 (A)
_0259_: _0946_.4 (Y), _0949_.2 (A)
_0260_: _0947_.4 (Y), _0948_.1 (B), _1020_.1 (B), _1025_.6 (C), _1028_.6 (C)
_0261_: _0948_.4 (Y), _0949_.1 (B), _1021_.1 (A), _1191_.6 (C)
_0262_: _0949_.4 (Y), _0953_.3 (B)
_0263_: _0950_.4 (Y), _0952_.2 (A), _1096_.1 (B), _1109_.1 (A), _1115_.1 (A), _1231_.1 (A)
_0264_: _0951_.4 (Y), _0952_.1 (B), _1118_.2 (A), _1120_.6 (C), _1128_.1 (B), _1131_.6 (C), _1231_.3 (B)
_0265_: _0952_.4 (Y), _0953_.6 (C)
_0266_: _0953_.4 (Y), _0960_.3 (B), _1080_.1 (A)
_0267_: _0954_.4 (Y), _0955_.1 (I1)
_0268_: _0955_.4 (Y), _0956_.6 (C)
_0269_: _0956_.4 (Y), _0959_.3 (B)
_0270_: _0957_.4 (Y), _0958_.6 (C)
_0271_: _0958_.4 (Y), _0959_.6 (C)
_0272_: _0959_.4 (Y), _1254__and_or.3 (B)
_0274_: _0960_.6 (C), _1254__and_or.4 (Y)
_0275_: _0960_.4 (Y), _0982_.1 (A)
_0276_: _0961_.4 (Y), _1072_.3 (B), _1091_.1 (A), fanout14.2 (A)
_0279_: _0963_.1 (B), _1337__mux2.4 (Y)
_0280_: _0963_.4 (Y), _0974_.1 (A)
_0281_: _0964_.4 (Y), _0965_.6 (C)
_0282_: _0965_.4 (Y), _0969_.1 (A)
_0283_: _0966_.4 (Y), _0968_.1 (A)
_0284_: _0967_.4 (Y), _0968_.3 (B)
_0285_: _0968_.4 (Y), _0969_.3 (B)
_0286_: _0969_.4 (Y), _0974_.3 (B)
_0287_: _0970_.4 (Y), _0971_.1 (I1)
_0288_: _0971_.4 (Y), _0972_.3 (B)
_0289_: _0972_.4 (Y), _0973_.1 (B)
_0290_: _0973_.4 (Y), _0974_.6 (C)
_0291_: _0974_.4 (Y), _0975_.1 (B), _0992_.1 (A)
_0292_: _0975_.4 (Y), _0982_.3 (B)
_0293_: _0976_.4 (Y), _0978_.3 (B)
_0294_: _0977_.4 (Y), _0978_.6 (C)
_0295_: _0978_.4 (Y), _0981_.2 (A), _1255__and_gate.2 (A)
_0296_: _0979_.4 (Y), _0980_.6 (C)
_0297_: _0980_.4 (Y), _0981_.1 (B)
_0298_: _0981_.4 (Y), _0982_.6 (C)
_0299_: _0983_.4 (Y), _0984_.1 (B), _1005_.6 (C), _1148_.6 (C)
_0300_: _0984_.4 (Y), _0990_.1 (A), _1045_.3 (B), _1229_.6 (C), _1257__and_or.3 (B)
_0301_: _0985_.4 (Y), _0987_.2 (A), _0988_.1 (B), _1046_.3 (B)
_0302_: _0986_.4 (Y), _0987_.1 (B)
_0303_: _0987_.4 (Y), _0990_.3 (B)
_0304_: _0988_.4 (Y), _0989_.6 (C), _1226_.6 (C)
_0305_: _0989_.4 (Y), _0990_.6 (C)
_0306_: _0990_.4 (Y), _0992_.3 (B)
_0307_: _0991_.4 (Y), _0992_.6 (C)
_0308_: _0992_.4 (Y), _1003_.2 (A)
_0309_: _0993_.4 (Y), _0995_.1 (A)
_0310_: _0994_.4 (Y), _0995_.3 (B)
_0311_: _0995_.4 (Y), _0997_.1 (A)
_0312_: _0996_.4 (Y), _0997_.3 (B)
_0313_: _0997_.4 (Y), _1002_.3 (B)
_0314_: _0998_.4 (Y), _1000_.3 (B)
_0315_: _0999_.4 (Y), _1000_.6 (C)
_0316_: _1000_.4 (Y), _1001_.6 (C)
_0317_: _1001_.4 (Y), _1002_.6 (C)
_0318_: _1002_.4 (Y), _1003_.1 (B)
_0319_: _1004_.4 (Y), _1005_.3 (B), _1025_.3 (B), _1032_.1 (B)
_0320_: _1005_.4 (Y), _1008_.3 (B)
_0321_: _1006_.4 (Y), _1007_.6 (C)
_0322_: _1007_.4 (Y), _1008_.6 (C), _1147_.2 (A)
_0323_: _1008_.4 (Y), _1010_.3 (B)
_0324_: _1009_.4 (Y), _1255__and_gate.1 (B)
_0326_: _1010_.6 (C), _1255__and_or.4 (Y)
_0327_: _1011_.4 (Y), _1039_.1 (A), _1256__and_or.1 (A)
_0328_: _1012_.4 (Y), _1256__and_or.3 (B)
_0330_: _1013_.4 (Y), _1014_.1 (B)
_0331_: _1015_.4 (Y), _1019_.2 (A)
_0332_: _1016_.4 (Y), _1018_.3 (B), _1099_.1 (A), _1151_.2 (A), _1195_.1 (A)
_0333_: _1017_.4 (Y), _1018_.6 (C), _1233_.1 (A)
_0334_: _1018_.4 (Y), _1019_.1 (B)
_0335_: _1019_.4 (Y), _1021_.3 (B)
_0336_: _1020_.4 (Y), _1021_.6 (C), _1068_.3 (B)
_0337_: _1021_.4 (Y), _1328__mux1.1 (I1)
_0338_: _1022_.4 (Y), _1024_.2 (A), _1026_.1 (B), _1069_.3 (B), _1082_.6 (C), _1197_.1 (A)
_0339_: _1023_.4 (Y), _1024_.1 (B)
_0340_: _1024_.4 (Y), _1328__mux1.6 (S), _1329__mux1.6 (S)
_0342_: _1025_.4 (Y), _1030_.1 (A)
_0343_: _1026_.4 (Y), _1030_.3 (B)
_0344_: _1027_.4 (Y), _1029_.1 (A), _1047_.2 (A)
_0345_: _1028_.4 (Y), _1029_.3 (B), _1074_.6 (C)
_0346_: _1029_.4 (Y), _1030_.6 (C)
_0347_: _1031_.4 (Y), _1033_.3 (B), _1036_.3 (B), _1098_.3 (B)
_0348_: _1032_.4 (Y), _1033_.6 (C)
_0349_: _1033_.4 (Y), _1329__mux1.1 (I1)
_0351_: _1034_.4 (Y), _1035_.6 (C)
_0352_: _1035_.4 (Y), _1039_.3 (B)
_0353_: _1036_.4 (Y), _1037_.6 (C), _1200_.6 (C)
_0354_: _1037_.4 (Y), _1038_.6 (C), _1042_.1 (B)
_0355_: _1038_.4 (Y), _1039_.6 (C)
_0356_: _1040_.4 (Y), _1041_.1 (B)
_0357_: _1041_.4 (Y), _1043_.3 (I0)
_0358_: _1042_.4 (Y), _1043_.1 (I1)
_0359_: _1044_.4 (Y), _1045_.6 (C)
_0360_: _1045_.4 (Y), _1048_.1 (A)
_0361_: _1046_.4 (Y), _1047_.1 (B)
_0362_: _1047_.4 (Y), _1048_.3 (B)
_0363_: _1048_.4 (Y), _1049_.1 (B), _1052_.1 (B), _1152_.3 (B)
_0364_: _1049_.4 (Y), _1051_.3 (B)
_0365_: _1050_.4 (Y), _1051_.6 (C)
_0366_: _1052_.4 (Y), _1055_.3 (B)
_0367_: _1053_.4 (Y), _1054_.6 (C)
_0368_: _1054_.4 (Y), _1055_.6 (C), _1227_.6 (C)
_0369_: _1056_.4 (Y), _1066_.1 (A), _1100_.6 (C), _1102_.1 (B), _1105_.1 (A)
_0370_: _1057_.4 (Y), _1058_.6 (C)
_0371_: _1058_.4 (Y), _1059_.3 (B)
_0372_: _1059_.4 (Y), _1064_.3 (B), _1089_.3 (B)
_0373_: _1060_.4 (Y), _1063_.2 (A)
_0374_: _1061_.4 (Y), _1330__and_gate.2 (A)
_0375_: _1062_.4 (Y), _1330__mux1.1 (I1)
_0377_: _1063_.1 (B), _1330__and_gate.4 (Y)
_0378_: _1063_.4 (Y), _1064_.6 (C), _1089_.6 (C)
_0379_: _1064_.4 (Y), _1066_.3 (B), _1111_.1 (A)
_0380_: _1065_.4 (Y), _1066_.6 (C), _1104_.1 (A), _1105_.6 (C)
_0381_: _1066_.4 (Y), _1071_.1 (A)
_0382_: _1067_.4 (Y), _1068_.6 (C)
_0383_: _1068_.4 (Y), _1069_.6 (C)
_0384_: _1069_.4 (Y), _1071_.3 (B)
_0385_: _1070_.4 (Y), _1071_.6 (C)
_0386_: _1071_.4 (Y), _1076_.2 (A)
_0388_: _1075_.1 (A), _1257__and_or.4 (Y)
_0389_: _1072_.4 (Y), _1073_.1 (I1)
_0390_: _1073_.4 (Y), _1075_.3 (B)
_0391_: _1074_.4 (Y), _1075_.6 (C)
_0392_: _1075_.4 (Y), _1076_.1 (B)
_0393_: _1077_.4 (Y), _1078_.2 (A), _1082_.1 (A), _1093_.6 (C)
_0394_: _1078_.4 (Y), _1080_.3 (B)
_0395_: _1079_.4 (Y), _1080_.6 (C), _1081_.1 (B), _1141_.6 (C)
_0396_: _1080_.4 (Y), _1095_.1 (A)
_0397_: _1081_.4 (Y), _1082_.3 (B)
_0398_: _1082_.4 (Y), _1088_.1 (A)
_0399_: _1083_.4 (Y), _1088_.3 (B)
_0400_: _1084_.4 (Y), _1085_.6 (C), _1090_.6 (C), _1116_.1 (B)
_0401_: _1085_.4 (Y), _1087_.3 (B), _1119_.1 (B)
_0402_: _1086_.4 (Y), _1087_.6 (C)
_0403_: _1087_.4 (Y), _1088_.6 (C)
_0404_: _1088_.4 (Y), _1095_.3 (B)
_0405_: _1089_.4 (Y), _1090_.3 (B), _1105_.3 (B)
_0406_: _1090_.4 (Y), _1091_.6 (C), _1114_.1 (B)
_0407_: _1091_.4 (Y), _1094_.2 (A)
_0408_: _1092_.4 (Y), _1093_.3 (B)
_0409_: _1093_.4 (Y), _1094_.1 (B)
_0410_: _1094_.4 (Y), _1095_.6 (C)
_0411_: _1096_.4 (Y), _1101_.1 (A)
_0412_: _1097_.4 (Y), _1098_.6 (C), _1195_.6 (C), _1231_.6 (C)
_0413_: _1098_.4 (Y), _1099_.6 (C)
_0414_: _1099_.4 (Y), _1101_.3 (B)
_0415_: _1100_.4 (Y), _1101_.6 (C), _1110_.3 (B)
_0416_: _1101_.4 (Y), _1106_.1 (A)
_0417_: _1102_.4 (Y), _1104_.3 (B)
_0418_: _1103_.4 (Y), _1104_.6 (C)
_0419_: _1104_.4 (Y), _1106_.3 (B)
_0420_: _1105_.4 (Y), _1106_.6 (C), _1145_.2 (A)
_0421_: _1107_.4 (Y), _1108_.1 (B), _1143_.3 (B)
_0422_: _1108_.4 (Y), _1111_.3 (B)
_0423_: _1109_.4 (Y), _1110_.6 (C)
_0424_: _1110_.4 (Y), _1111_.6 (C)
_0425_: _1112_.4 (Y), _1113_.1 (B)
_0426_: _1113_.4 (Y), _1115_.3 (B)
_0427_: _1114_.4 (Y), _1115_.6 (C), _1129_.1 (A), _1138_.1 (A)
_0428_: _1115_.4 (Y), _1331__and_gate.2 (A)
_0429_: _1116_.4 (Y), _1117_.1 (B)
_0430_: _1117_.4 (Y), _1331__mux1.3 (I0)
_0431_: _1118_.4 (Y), _1331__mux1.1 (I1)
_0433_: _1119_.4 (Y), _1122_.2 (A), _1134_.2 (A), _1142_.1 (A)
_0434_: _1120_.4 (Y), _1121_.1 (B)
_0435_: _1121_.4 (Y), _1122_.1 (B)
_0436_: _1122_.4 (Y), _1130_.2 (A)
_0437_: _1123_.4 (Y), _1124_.1 (B), _1140_.3 (B)
_0438_: _1124_.4 (Y), _1125_.6 (C), _1137_.6 (C)
_0439_: _1125_.4 (Y), _1129_.3 (B)
_0440_: _1126_.4 (Y), _1127_.2 (A)
_0441_: _1127_.4 (Y), _1332__mux1.1 (I1)
_0442_: _1128_.4 (Y), _1332__mux1.6 (S)
_0444_: _1129_.6 (C), _1332__and_gate.4 (Y)
_0445_: _1129_.4 (Y), _1130_.1 (B)
_0446_: _1131_.4 (Y), _1132_.1 (B), _1141_.3 (B), _1143_.6 (C), _1333__mux1.6 (S)
_0447_: _1132_.4 (Y), _1133_.1 (B)
_0448_: _1133_.4 (Y), _1134_.1 (B)
_0449_: _1134_.4 (Y), _1139_.2 (A)
_0450_: _1135_.4 (Y), _1136_.1 (B), _1141_.1 (A), _1143_.1 (A)
_0451_: _1136_.4 (Y), _1333__mux1.1 (I1)
_0453_: _1138_.3 (B), _1333__and_gate.4 (Y)
_0454_: _1137_.4 (Y), _1138_.6 (C)
_0455_: _1138_.4 (Y), _1139_.1 (B)
_0456_: _1140_.4 (Y), _1142_.3 (B)
_0457_: _1141_.4 (Y), _1142_.6 (C)
_0458_: _1142_.4 (Y), _1144_.3 (B)
_0459_: _1143_.4 (Y), _1144_.6 (C)
_0460_: _1144_.4 (Y), _1145_.1 (B)
_0461_: _1146_.4 (Y), _1147_.1 (B)
_0462_: _1147_.4 (Y), _1150_.2 (A)
_0463_: _1148_.4 (Y), _1149_.6 (C)
_0464_: _1149_.4 (Y), _1150_.1 (B)
_0465_: _1151_.4 (Y), _1152_.6 (C)
_0466_: _1152_.4 (Y), _1155_.2 (A)
_0467_: _1153_.4 (Y), _1154_.1 (B)
_0468_: _1154_.4 (Y), _1155_.1 (B)
_0469_: _1156_.4 (Y), _1160_.2 (A)
_0470_: _1157_.4 (Y), _1158_.6 (C), _1188_.6 (C)
_0471_: _1158_.4 (Y), _1159_.1 (B), _1163_.1 (B), _1183_.6 (C)
_0472_: _1159_.4 (Y), _1160_.1 (B)
_0473_: _1161_.4 (Y), _1162_.1 (B)
_0474_: _1162_.4 (Y), _1167_.2 (A)
_0475_: _1163_.4 (Y), _1166_.3 (B), _1169_.6 (C), _1258__and_or.1 (A)
_0476_: _1164_.4 (Y), _1165_.1 (B), _1170_.6 (C), _1174_.1 (B), _1176_.3 (B), _1179_.6 (C), _1186_.6 (C), _1187_.6 (C)
_0477_: _1165_.4 (Y), _1166_.6 (C), _1184_.1 (B), _1258__and_gate.1 (B)
_0478_: _1166_.4 (Y), _1167_.1 (B)
_0479_: _1168_.4 (Y), _1170_.1 (A)
_0480_: _1169_.4 (Y), _1170_.3 (B), _1175_.1 (B), _1178_.2 (A), _1181_.1 (B)
_0481_: _1170_.4 (Y), _1173_.2 (A)
_0482_: _1171_.4 (Y), _1172_.1 (B)
_0483_: _1172_.4 (Y), _1173_.1 (B)
_0484_: _1174_.4 (Y), _1175_.2 (A), _1177_.1 (B)
_0485_: _1175_.4 (Y), _1176_.6 (C)
_0486_: _1177_.4 (Y), _1178_.1 (B)
_0487_: _1179_.4 (Y), _1180_.1 (B), _1182_.3 (B)
_0488_: _1180_.4 (Y), _1181_.2 (A), _1185_.3 (B)
_0489_: _1181_.4 (Y), _1182_.6 (C)
_0490_: _1183_.4 (Y), _1184_.2 (A)
_0491_: _1184_.4 (Y), _1185_.6 (C)
_0492_: _1186_.4 (Y), _1258__and_or.3 (B)
_0494_: _1187_.4 (Y), _1190_.3 (B)
_0495_: _1188_.4 (Y), _1189_.1 (B)
_0496_: _1189_.4 (Y), _1190_.6 (C), _1193_.6 (C)
_0497_: _1191_.4 (Y), _1193_.1 (A)
_0498_: _1192_.4 (Y), _1193_.3 (B)
_0499_: _1194_.4 (Y), _1198_.3 (B)
_0500_: _1195_.4 (Y), _1197_.3 (B)
_0501_: _1196_.4 (Y), _1197_.6 (C)
_0502_: _1197_.4 (Y), _1198_.6 (C)
_0503_: _1198_.4 (Y), _1199_.1 (B)
_0504_: _1200_.4 (Y), _1259__mux.6 (S), _1261__mux.6 (S), _1266__mux.6 (S), _1271__mux.6 (S), max_cap10.2 (A)
_0506_: _1202_.4 (Y), _1203_.1 (B), _1205_.3 (B), _1206_.6 (C), _1210_.6 (C), _1213_.6 (C)
_0507_: _1203_.4 (Y), _1204_.1 (B)
_0508_: _1205_.4 (Y), _1207_.3 (B)
_0509_: _1206_.4 (Y), _1207_.6 (C), _1208_.1 (B)
_0510_: _1208_.4 (Y), _1209_.1 (B)
_0511_: _1210_.4 (Y), _1211_.1 (B)
_0512_: _1211_.4 (Y), _1212_.1 (B)
_0513_: _1213_.4 (Y), _1214_.1 (B), _1216_.1 (B)
_0514_: _1214_.4 (Y), _1215_.1 (B)
_0515_: _1216_.4 (Y), _1217_.1 (B), _1219_.3 (B), _1220_.6 (C)
_0516_: _1217_.4 (Y), _1218_.1 (B)
_0517_: _1219_.4 (Y), _1221_.3 (B)
_0518_: _1220_.4 (Y), _1221_.6 (C)
_0519_: _1222_.4 (Y), _1223_.6 (C)
_0520_: _1223_.4 (Y), _1224_.6 (C)
_0521_: _1225_.4 (Y), _1235_.2 (A)
_0522_: _1226_.4 (Y), _1228_.3 (B)
_0523_: _1227_.4 (Y), _1249_.6 (C), fanout1.2 (A)
_0524_: _1228_.4 (Y), _1234_.1 (A)
_0525_: _1229_.4 (Y), _1234_.3 (B)
_0526_: _1230_.4 (Y), _1233_.3 (B)
_0527_: _1231_.4 (Y), _1232_.6 (C)
_0528_: _1232_.4 (Y), _1233_.6 (C)
_0529_: _1233_.4 (Y), _1234_.6 (C)
_0530_: _1234_.4 (Y), _1235_.1 (B), _1240_.3 (B), _1244_.3 (B), _1248_.3 (B), _1252_.3 (B)
_0531_: _1235_.4 (Y), _1237_.3 (B), _1242_.3 (B), _1246_.3 (B), _1250_.3 (B)
_0532_: _1236_.4 (Y), _1237_.6 (C)
_0533_: _1238_.4 (Y), _1239_.6 (C), _1243_.6 (C), _1247_.6 (C), _1251_.6 (C)
_0534_: _1239_.4 (Y), _1240_.6 (C)
_0535_: _1241_.4 (Y), _1242_.6 (C)
_0536_: _1243_.4 (Y), _1244_.6 (C)
_0537_: _1245_.4 (Y), _1246_.6 (C)
_0538_: _1247_.4 (Y), _1248_.6 (C)
_0539_: _1249_.4 (Y), _1250_.6 (C)
_0540_: _1251_.4 (Y), _1252_.6 (C)
_1254__a_and: _1254__and_gate.4 (Y), _1254__and_or.6 (C)
_1255__a_and: _1255__and_gate.4 (Y), _1255__and_or.6 (C)
_1256__a_and: _1256__and_gate.4 (Y), _1256__and_or.6 (C)
_1257__a_and: _1257__and_gate.4 (Y), _1257__and_or.6 (C)
_1258__a_and: _1258__and_gate.4 (Y), _1258__and_or.6 (C)
_1259__d_selected: _1259__dff.3 (D), _1259__mux.4 (Y)
_1260__d_selected: _1260__dff.3 (D), _1260__mux.4 (Y)
_1261__d_selected: _1261__dff.3 (D), _1261__mux.4 (Y)
_1262__d_selected: _1262__dff.3 (D), _1262__mux.4 (Y)
_1263__d_selected: _1263__dff.3 (D), _1263__mux.4 (Y)
_1264__d_selected: _1264__dff.3 (D), _1264__mux.4 (Y)
_1265__d_selected: _1265__dff.3 (D), _1265__mux.4 (Y)
_1266__d_selected: _1266__dff.3 (D), _1266__mux.4 (Y)
_1267__d_selected: _1267__dff.3 (D), _1267__mux.4 (Y)
_1268__d_selected: _1268__dff.3 (D), _1268__mux.4 (Y)
_1269__d_selected: _1269__dff.3 (D), _1269__mux.4 (Y)
_1270__d_selected: _1270__dff.3 (D), _1270__mux.4 (Y)
_1271__d_selected: _1271__dff.3 (D), _1271__mux.4 (Y)
_1272__d_selected: _1272__dff.3 (D), _1272__mux.4 (Y)
_1273__d_selected: _1273__dff.3 (D), _1273__mux.4 (Y)
_1328__mux1_data: _1328__and_gate.1 (B), _1328__mux1.4 (Y)
_1329__mux1_data: _1329__and_gate.1 (B), _1329__mux1.4 (Y)
_1330__mux1_data: _1330__and_gate.1 (B), _1330__mux1.4 (Y)
_1331__mux1_data: _1331__and_gate.1 (B), _1331__mux1.4 (Y)
_1332__mux1_data: _1332__and_gate.1 (B), _1332__mux1.4 (Y)
_1333__mux1_data: _1333__and_gate.1 (B), _1333__mux1.4 (Y)
_1334__mux1_data: _1334__and_gate.1 (B), _1334__mux1.4 (Y)
_1335__mux1_data: _1335__and_gate.1 (B), _1335__mux1.4 (Y)
_1336__mux1_data: _1336__and_gate.1 (B), _1336__mux1.4 (Y)
_1337__mux1_data: _1337__mux1.4 (Y), _1337__mux2.1 (I1)
_1338__mux1_data: _1338__mux1.4 (Y), _1338__mux2.1 (I1)
_1339__mux1_data: _1339__mux1.4 (Y), _1339__mux2.1 (I1)
_1340__mux1_data: _1340__mux1.4 (Y), _1340__mux2.1 (I1)
_1341__mux1_data: _1341__mux1.4 (Y), _1341__mux2.1 (I1)
_1342__mux1_data: _1342__mux1.4 (Y), _1342__mux2.1 (I1)
_1343__mux1_data: _1343__mux1.4 (Y), _1343__mux2.1 (I1)
clknet_0_i_clk: clkbuf_3_0__f_i_clk.2 (A), clkbuf_3_1__f_i_clk.2 (A), clkbuf_3_2__f_i_clk.2 (A), clkbuf_3_3__f_i_clk.2 (A), clkbuf_3_4__f_i_clk.2 (A), clkbuf_3_5__f_i_clk.2 (A), clkbuf_3_6__f_i_clk.2 (A), clkbuf_3_7__f_i_clk.2 (A), delaybuf_0_.4 (Y)
clknet_0_i_clk_regs: clkbuf_0_i_clk_regs.4 (Y), clkbuf_1_0__f_i_clk_regs.2 (A)
clknet_1_0__leaf_i_clk_regs: _1253__15.2 (A), clkbuf_1_0__f_i_clk_regs.4 (Y)
clknet_3_0__leaf_i_clk: _1264__dff.1 (CLK), _1265__dff.1 (CLK), _1267__dff.1 (CLK), _1268__dff.1 (CLK), _1270__dff.1 (CLK), _1272__dff.1 (CLK), _1281__dff.1 (CLK), _1286__dff.1 (CLK), _1287__dff.1 (CLK), clkbuf_3_0__f_i_clk.4 (Y), clkload0.2 (A)
clknet_3_1__leaf_i_clk: _1259__dff.1 (CLK), _1260__dff.1 (CLK), _1262__dff.1 (CLK), _1263__dff.1 (CLK), _1269__dff.1 (CLK), _1277__dff.1 (CLK), _1279__dff.1 (CLK), _1280__dff.1 (CLK), _1282__dff.1 (CLK), clkbuf_3_1__f_i_clk.4 (Y), clkload1.2 (A)
clknet_3_2__leaf_i_clk: _1311__dff.1 (CLK), _1312__dff.1 (CLK), _1314__dff.1 (CLK), _1315__dff.1 (CLK), _1316__dff.1 (CLK), _1317__dff.1 (CLK), clkbuf_3_2__f_i_clk.4 (Y), clkload2.2 (A)
clknet_3_3__leaf_i_clk: _1278__dff.1 (CLK), _1285__dff.1 (CLK), _1302__dff.1 (CLK), _1303__dff.1 (CLK), _1304__dff.1 (CLK), _1305__dff.1 (CLK), _1306__dff.1 (CLK), _1313__dff.1 (CLK), clkbuf_3_3__f_i_clk.4 (Y), clkload3.2 (A)
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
